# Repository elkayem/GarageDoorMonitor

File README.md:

# GarageDoorMonitor

The Garage Door Monitor continously monitors whether your garage door is closed, and sends out an email or text message if it has been left open for more than 15 minutes.  It uses the popular ESP8266 WiFi module, and relays messages to you via the IFTTT web service. In our household, we have accidentally left the garage door open on multiple occasions, and this device has saved our bacon more than once.  

Features:
* Email and/or text sent every 15 minutes when your door has been left open, notifying you what time it was opened and how long
* Email/text sent once your door has been closed
* Synchronization with NIST time
* Enable/disable button, which can temporarily disable the monitor
* RGB LED indicating monitor status
* OLED Display
* Configurable settings via WiFi access point
* (Optional) logging of door status via Adafruit IO

The following parts are required, as pictured below:
* NodeMCU V1.0 development board (sometimes also listed as v2 at online shops such as eBay or AliExpress)
* 5V Micro-USB power supply (500 mA or higher)
* Normally Open magnetic switch
* (2) Female headers
* Common Anode RGB LED
* Screw Terminal Block (2 pin 3.5mm Pitch)
* 6x6mm tactile button
* 10K resistor
* (3) 300 Ohm resistors
* (Optional) 4-pin male header
* (Optional) Printed Circuit Board (Eagle files included)
* (Optional) 128x64 I2C OLED Display  (Preferably a two-color display, e.g., yellow/blue)

The PCB is indicated as optional, since the circuit is simple enough to hand solder on a PCB breadboard if desired (schematic shown below).  An OLED display as shown below can enhance the monitor, but is not necessary. There are also two different variations of 3D printed cases provided, one which is used when there is no OLED display, and the other to be used with an OLED.  The non-OLED case was designed in OpenSCAD, and the OLED case (pictured below) was designed in Sketchup 2017.

# Instructions
1. Set up an account at IFTTT.com.  Add the "Webhook" service to your account.  Record the Webhook service API Key for later use, which can be found under the Webhook service settings.  It is a long character sequence following at the end of the URL in Settings, i.e., the character sequence appearing at API_KEY in https://maker.ifttt.com/use/API_KEY.  Note: once the key is created, do not press the "Edit connection" link, or it will create a new key and remove the old one.
2. In IFTTT, create a new applet.  You should see a sentence that says "if +this then that".  Press "+this", and choose the "Webhook" service.  Select the "Receive a web request" trigger.  Call the event "door_open", and create the trigger. Next, press "+that" (from the "if this then that" sentence) and choose the Gmail service.  Select the "Send and email" action.    Choose Gmail as the action (the "then that" part).  Place the desired emails on the To line (text messages can also be sent depending on the provider, e.g., as xxxxxxxxxx@txt.att.net).  Fill out the Subject as: Garage Door Open for  "{{Value1}}" Minutes.  Fill out the body as: The Garage Door was opened at {{Value1}} and has been open for {{Value2}} minutes.  Press the "Create action" buttong.  It should look as shown below:

3. Create another applet in IFTTT with Webhook as the trigger and Gmail as the action.  Call the Webhook event name "door_closed".  Put in the desired email(s) for the Gmail action and fill out the Subject and Body as shown below:

4. Create an additional applet which will send out an email at midnight every day giving you confirmation that your door monitor is still working, and the last time the garage door was closed.  This applet also has Webhook as the trigger and Gmail as the action. Call the Webhook event name "door_monitor_active".  Put in the desired email(s) for the Gmail action and fill out the Subject and Body as shown below:

5. (Optional) If using Adafruit IO, set up and account at https://io.adafruit.com/.  Record your username and Adafruit IO key for later use.  Add a feed called "garage-door" to your Adafruit IO account.
6. Solder together your garage door monitor, install it in your garage, and plug it in.  If using an OLED display, connect display to the I2C headers using 4" female-female jumper wires, taking special care to match the 3V3 and GND on the display to the board.  Swapping 3V3 and GND will fry your OLED.    
    * **Note #1:** Take care to solder the RGB LED pins in the correct order.  The longest pin is the common anode, which should be soldered in the hole second from the left, where the NodeMCU is on the left side of the board.  The LED case also has a flat edge, which should match the flat edge shown on the board silkscreen.
    * **Note #2:** If you happen to have one of the old PCBs that does not include a 10K resistor on the front of the PCB, you will need to solder a 10K pull-up resistor on the back of the PCB as pictured [here](/images/IMG_2138.JPG).  The PCB pictured on this page above is the old design, with only three resistors on the front, whereas the new PCB has four resistors on the front.  
7. Print out a case on a 3D printer, or design your own.  Two case designs are provided in the "cases" folder. Assemble case and electronics.
8. Flash software to ESP8266 using a micro-USB cable.  This can be done one of two ways: a) Use the compiled .bin files included in the repository, or b) compile and flash the firmware using the Arduino IDE.  I have included two different compiled version.  The file monitor_with_aio.bin should be used if you wish to log the garage door status using Adafruit IO.  The file monitor_without_aio.bin is used if you do not wish to log the status.  Both support the IFTTT web service to email and text message you.  Both also support the OLED screen.  If using one of these files, I recommend using esptool at https://github.com/espressif/esptool to flash the esp8266.  After installing esptool, the following line is used to flash the ESP8266:

    `esptool.py --port COM6 write_flash 0x0000 monitor_without_aio.bin`
  
    where COM6 should be replaced by whatever com port your device is plugged into. (In Windows, this is discoverable using the Device Monitor.) 

    If compiling and flashing using the Arduino IDE, please see the Special Instructions for Compiling and Flashing Firmware Using Arduino IDE at the end of this Readme file.

9. Power garage door monitor using a 5V micro-USB power supply.  When powered for the first time, the monitor will create a WiFi access point called GARAGE_DOOR.  Look for a WiFi network called GARAGE_DOOR on your computer, tablet, or phone and connect to it (default password is PASSWORD, which can be modified in the source code).  (If you don't see one within 30 seconds, it may need to have its settings reset.  Hold down the button for 5 seconds and then cycle the power.)  Your web browser may automatically open up a web page at 192.168.4.1.  If not, connect to this IP address in a browser.  The web page will appear as shown below.  Press "Configure WiFi" and enter in your SSID and password credentials as shown below.  Add the IFTTT API_KEY that you recorded from IFTTT.  Enter in your time zone as indicated, and whether you wish to have the monitor automatically adjust for daylight savings time using US DST rules.  (Enter Y even if it is not currently DST as it will use the date to determine when to adust.) If using the Adafruit IO option, you will also see an entry for Adafruit IO username and key.  Press "save" and the garage door monitor will automatically connect to your WiFi network.

10. Install in your garage and enjoy!  

The LED will be red at turn-on, and will change to green once it has connected to WiFi and synced with NIST time.  When the garage door is shut, the light will remain green.  If open, it will change to magenta for 15 minutes, and will then change to red after it has sent out its first email.  Pressing the tactile button will cause the light to blink blue, and the monitor will not send any emails for 2 hours, or whenever the button is pushed again, which ever comes first.  Any failure to connect to WiFi will cause the monitor to blink red until it is able to reconnect.

The OLED will automatically turn off after five minutes of inactivity while the garage door is closed. This is to prevent OLED burn-in. This time can be extended by changing the OLED_TIMEOUT duration in the code. 

If you ever wish to reset the SSID credentials, IFTTT key, or other settings, press the button for 5 seconds and power cycle.  Follow instructions 

# Special Instructions for Compiling and Flashing Firmware Using Arduino IDE
1. Configure Arduino IDE
  1. Install Arduino IDE 1.8.15 (or later) from arduino.cc
  2. Open File>Preferences, and enter the following URL into "Additional Board Manager URLs": http://arduino.esp8266.com/stable/package_esp8266com_index.json
  3. Open Tools>Board>Board Manager and install the esp8266 boards.  I am currently using v3.0.2, but later versions should also work.
  4. In the Tools menu, configure Board: NodeMCU 1.0 (ESP-12E Module), CPU Frequency: 80 MHz, Upload Speed: 115200.
2. (Optional) If logging is desired, uncomment #define ADAFRUIT_IO and 
3. Install the following libraries.  I have indicated which versions I am currently using, though in most cases later versions should work: NTPClient (3.2.0), WiFi (1.2.7), WiFiManager (2.0.3-alpha), Time (1.6.1), Timezone (1.2.4), ArduinoJson (6.8.3), Adafruit_MQTT (2.4.2), Adafruit_GFX (1.10.10), and Adafruit_SSD1306 (2.4.6).  All of these libraries are added through the Library Manager (Sketch > Include Library > Manage Libraries).
4. If not using an OLED display, you can comment out the line #define OLED_DISPLAY in the sketch.  Otherwise, make sure the libraries Adafruit_GFX and Adafruit_SSD1306 are installed.   
5. Connect the NodeMCU board to your computer using a micro USB cable, and set Tools>Port to the new port that appears.  Your computer should automatically install the driver, but if it does not, you may need to manually download and install the CP2102 driver from http://www.silabs.com/products/mcu/pages/usbtouartbridgevcpdrivers.aspx.  
6. Press the Upload button to compile the sketch and upload to the NodeMCU.  The most common reason for failing to compile are an selecting the wrong board or not installing all the required libraries.

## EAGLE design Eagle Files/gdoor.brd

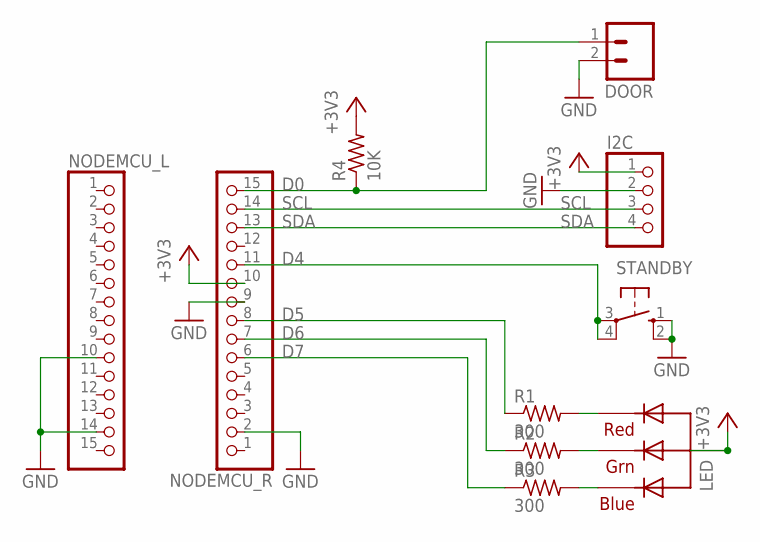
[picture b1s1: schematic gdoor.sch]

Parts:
DOOR: M025MM; SCREWTERMINAL-5MM-2
I2C: PINHD-1X4; 1X04
LED: RGBLED_CA-5MM; LED5MMRGB
NODEMCU_L: PINHD-1X15; 1X15
NODEMCU_R: PINHD-1X15; 1X15
R1, R2, R3: 300; 0207/10
R4: 10K; 0207/10
STANDBY: 10-XX; B3F-10XX

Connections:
+3V3: I2C.1, LED.2 (VCC), NODEMCU_R.10, R4.2
BLUE: LED.4 (BLUE), R3.2
D0: DOOR.1, NODEMCU_R.15, R4.1
D4: NODEMCU_R.11, STANDBY.3, STANDBY.4 (P1)
D5: NODEMCU_R.8, R1.1
D6: NODEMCU_R.7, R2.1
D7: NODEMCU_R.6, R3.1
GND: DOOR.2, I2C.2, NODEMCU_L.10, NODEMCU_L.14, NODEMCU_R.2, NODEMCU_R.9, STANDBY.1 (S), STANDBY.2 (S1)
GRN: LED.3 (GREEN), R2.2
RED: LED.1 (RED), R1.2
SCL: I2C.3, NODEMCU_R.14
SDA: I2C.4, NODEMCU_R.13

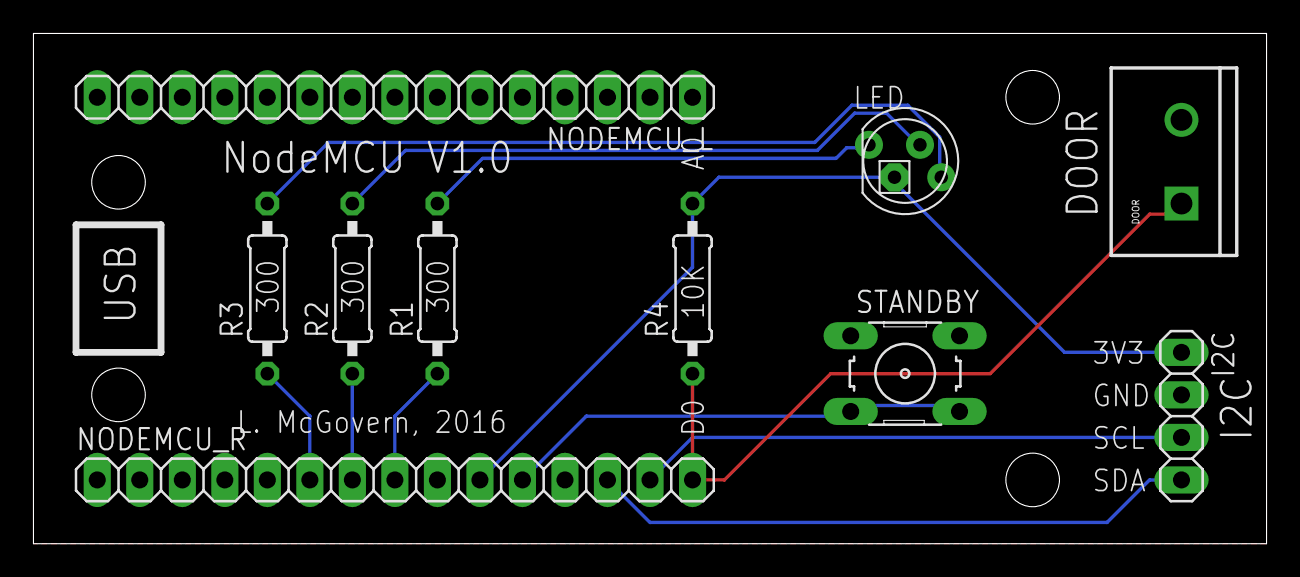
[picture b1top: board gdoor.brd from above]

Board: 2 copper layers, 73.7 x 30.5 mm, 10 parts (0 on the bottom side), 12 nets.

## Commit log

2016-12-31 Initial commit of code and schematic.
2016-12-31 Slight mod to readme. Instructions still needed.
2016-12-31 add image
2016-12-31 new images
2017-01-08 Fixed issue with standby button
2017-01-08 Adding GPL license
2017-01-21 Updated instructions
2017-01-21 Update instructions
2017-01-21 Add Gitter badge
2017-01-21 OpenSCAD and STL files
    Add files for a 3D printed case.
2017-02-02 Mounting plate and bottom with standoffs
    The bottom has standoffs positioned to match the screw holes in the
    board.
    Photos included.
2017-02-13 OLED Upgrade
2017-02-25 Add case for garage door monitor with OLED
2017-02-25 Update images
2017-03-29 Accidentally saved the bottom last time under this filename. This is the correct file.
2017-10-06 Improved button flexibility. Updated instructions.
2017-10-25 Update OLED mount
2018-04-20 Add WiFiManager compatibility
2018-05-26 Make IFTTT webhook calls more robust
2018-06-30 Standby mode mods
2018-11-21 Code and PCB modified for robustness
2021-09-05 Added OLED Timeout to prevent OLED burn-in. Updated code to work with ArduinoJson v6.

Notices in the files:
parts and their libraries:
SparkFun-Connectors: Licensing: Creative Commons ShareAlike 4.0 International - https://creativecommons.org/licenses/by-sa/4.0
